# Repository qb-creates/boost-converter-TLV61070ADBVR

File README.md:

# boost-converter-TLV61070ADBVR
Simple boost converter using the Texas Instrument TLV61070ADBVR

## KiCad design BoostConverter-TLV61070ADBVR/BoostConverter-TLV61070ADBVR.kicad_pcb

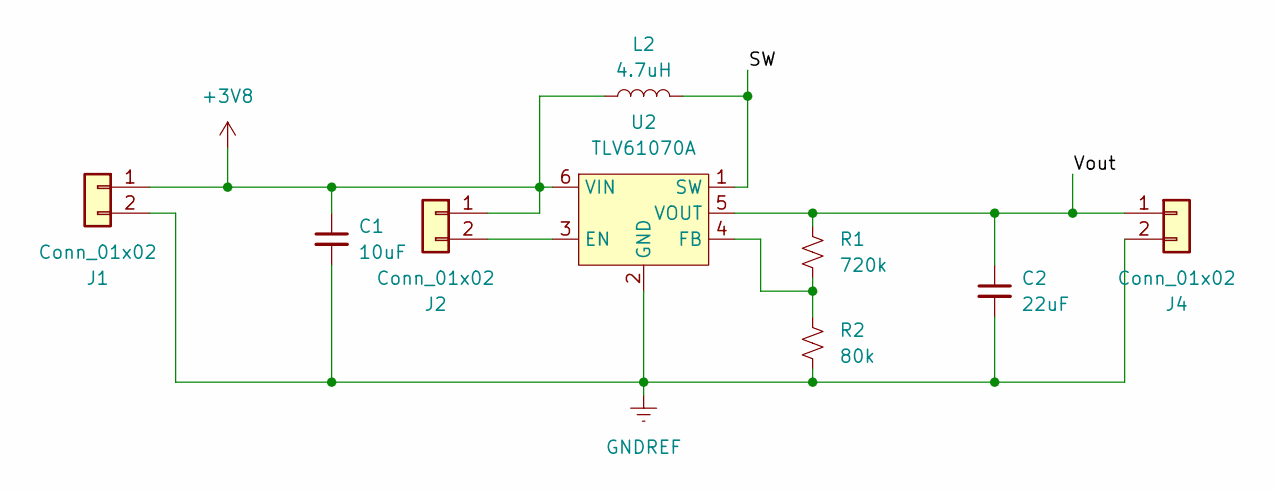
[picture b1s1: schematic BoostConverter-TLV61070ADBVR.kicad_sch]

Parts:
C1: 10uF; C_1206_3216Metric
C2: 22uF; C_1206_3216Metric
J1, J2, J4: Conn_01x02; PinHeader_1x02_P2.54mm_Vertical
L2: 4.7uH; Bourns SRP30xx
R1: 720k; R_0603_1608Metric_Pad0.98x0.95mm_HandSolder
R2: 80k; R_0603_1608Metric
U2: TLV61070A; SOT-23-6

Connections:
+3V8: C1.1, J1.1, J2.1, L2.1, U2.6 (VIN)
/SW: L2.2, U2.1 (SW)
/Vout: C2.1, J4.1, R1.1, U2.5 (VOUT)
GNDREF: C1.2, C2.2, J1.2, J4.2, R2.2, U2.2 (GND)
unnamed: J2.2, U2.3 (EN)
unnamed: R1.2, R2.1, U2.4 (FB)

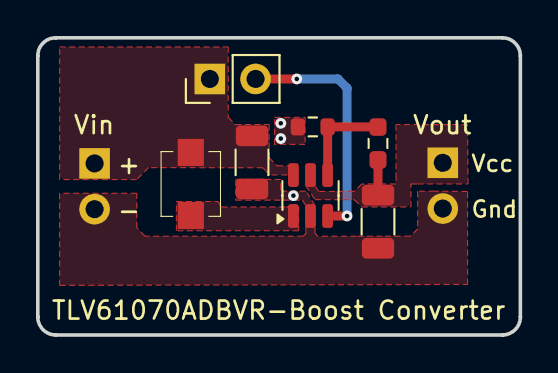
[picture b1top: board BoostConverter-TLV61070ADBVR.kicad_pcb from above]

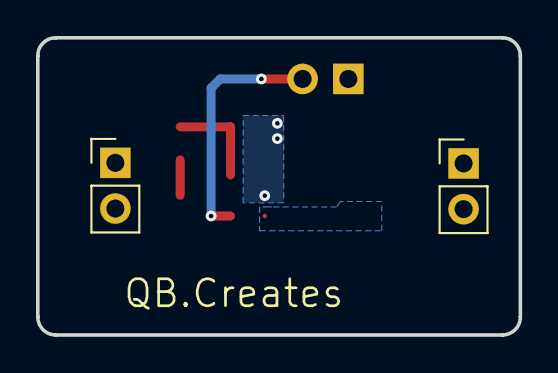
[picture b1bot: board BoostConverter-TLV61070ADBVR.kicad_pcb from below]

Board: 2 copper layers, 26.8 x 16.5 mm, 9 parts (2 on the bottom side), 6 nets.

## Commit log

2024-06-27 Adding project to the repo
2024-08-11 Added correct datasheet to the inductor. Added the inductor part number to the description
